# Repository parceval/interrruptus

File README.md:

# interrruptus
A simple Interrupt Controller and Timer made in Verilog

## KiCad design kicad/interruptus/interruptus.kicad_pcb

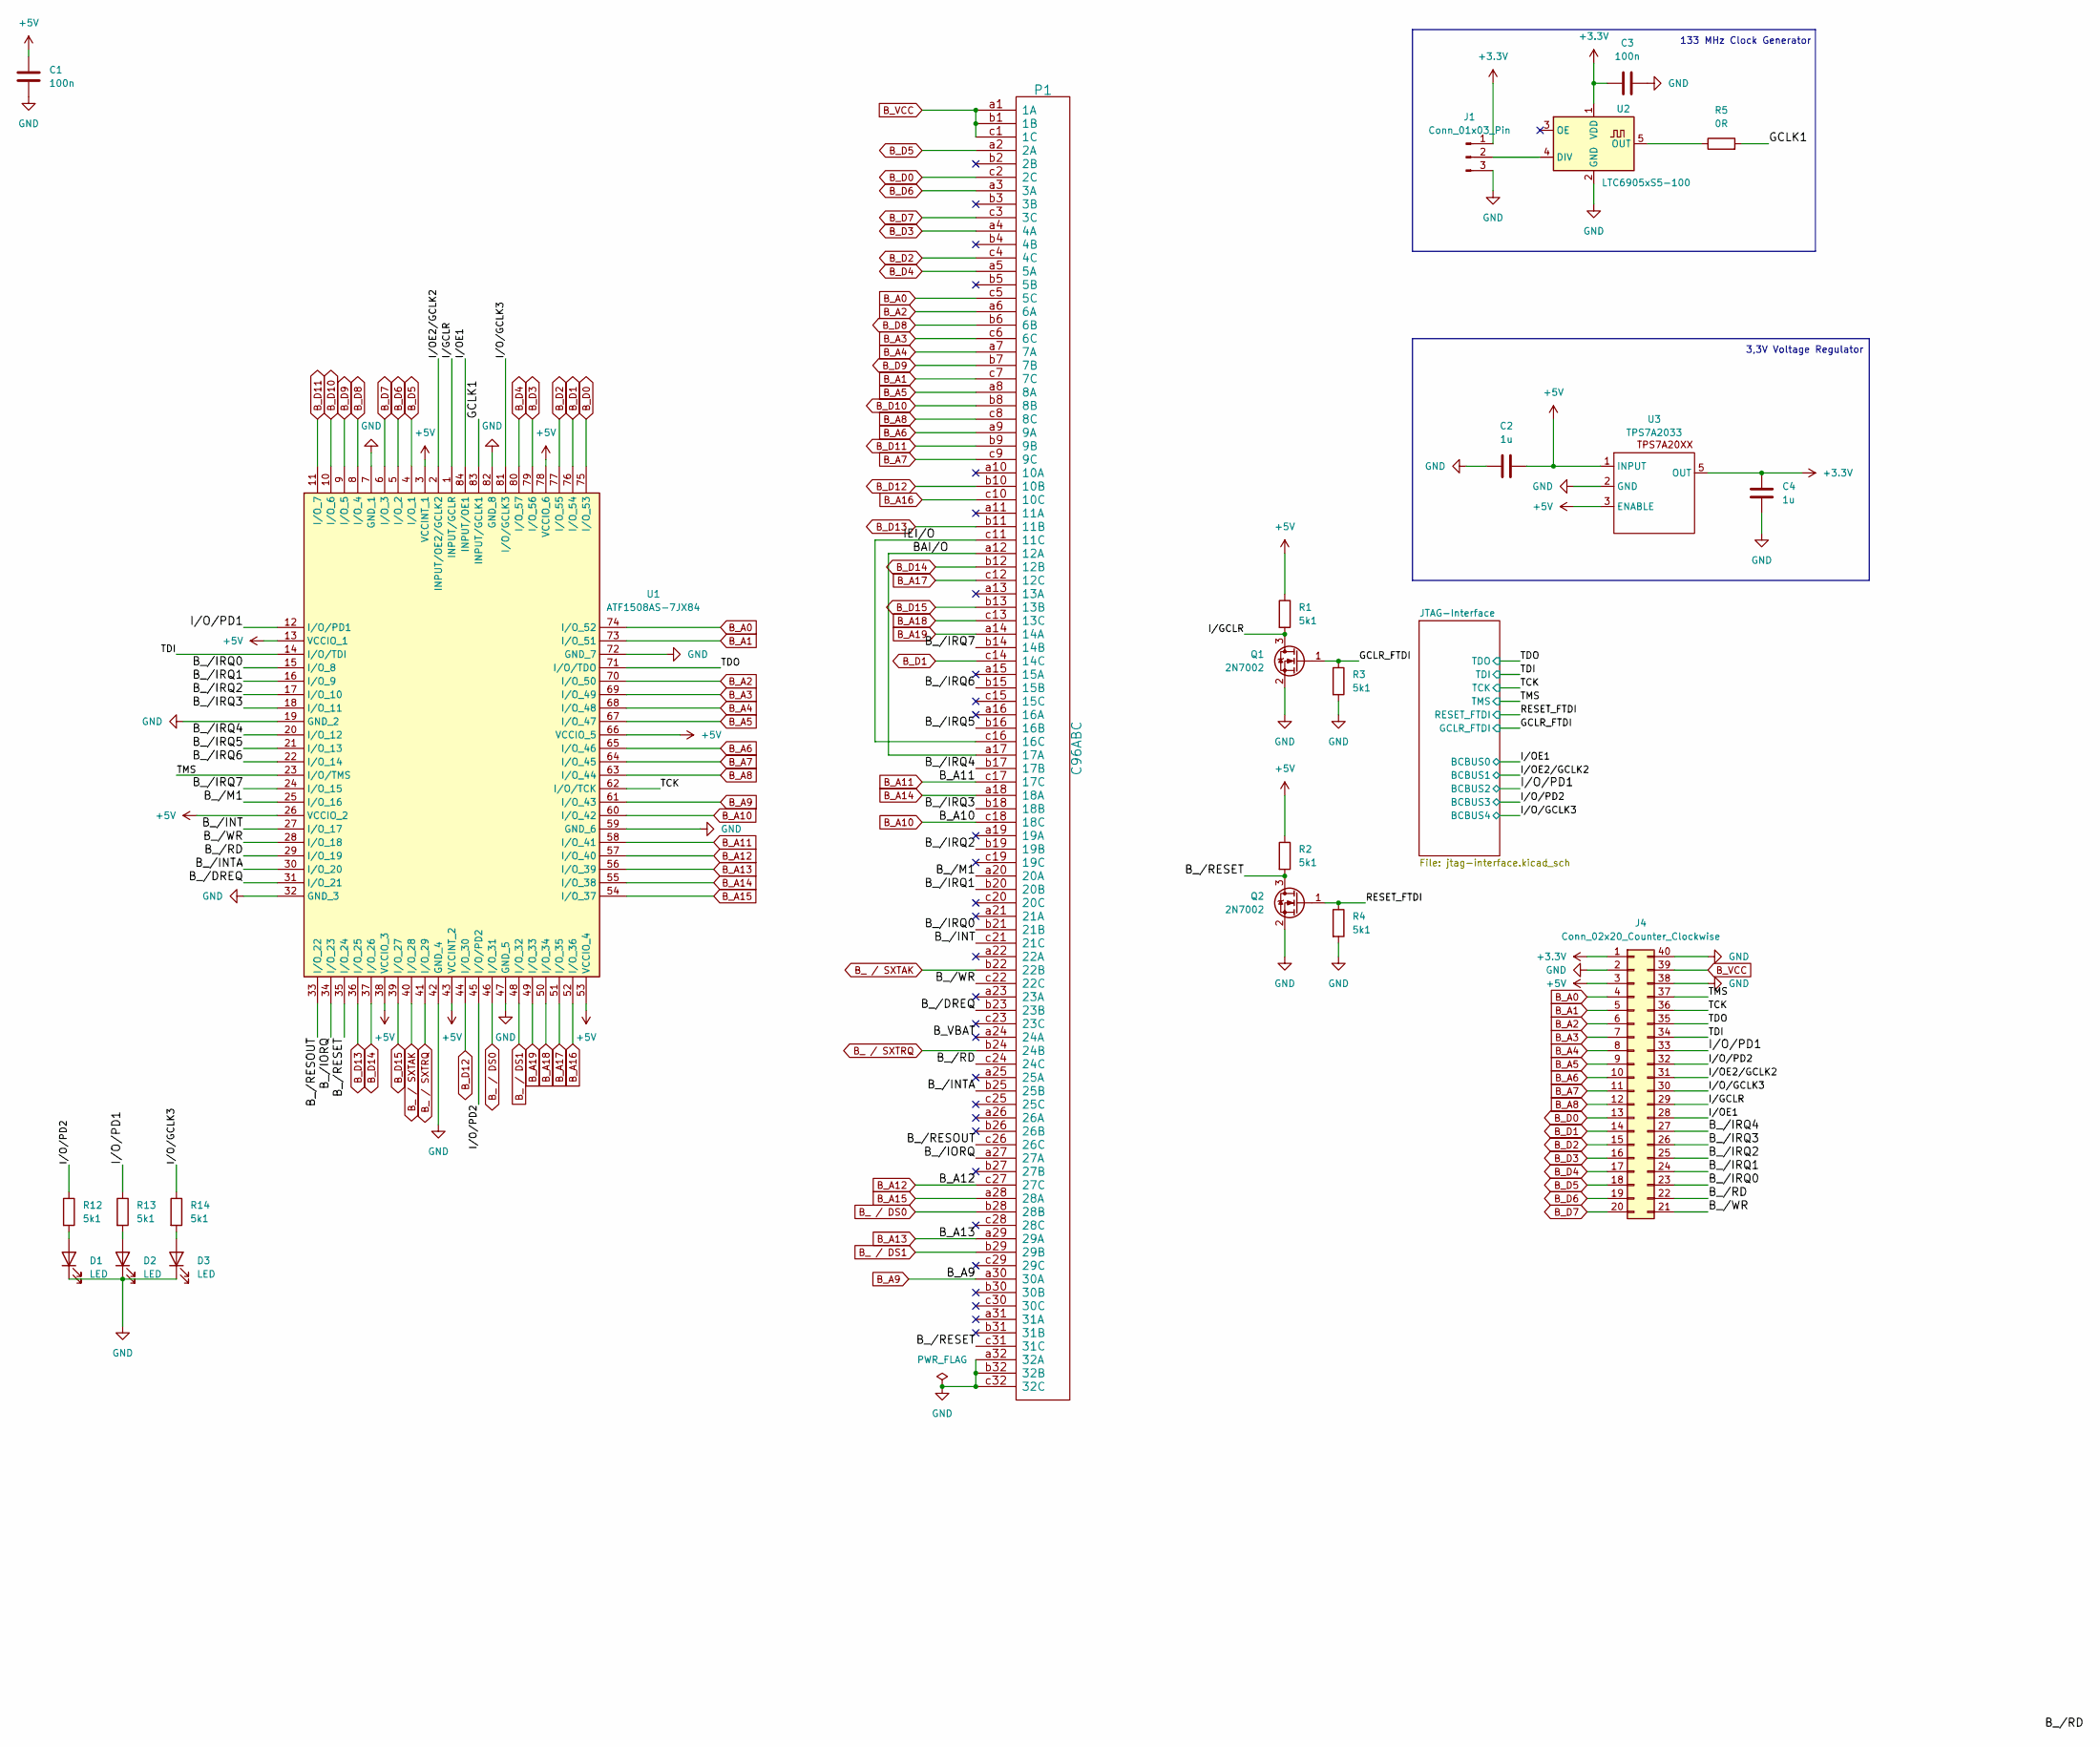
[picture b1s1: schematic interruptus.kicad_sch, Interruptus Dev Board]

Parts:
C1, C3: 100n; C_0603_1608Metric_Pad1.08x0.95mm_HandSolder
C2, C4: 1u; C_0603_1608Metric_Pad1.08x0.95mm_HandSolder
D1, D2, D3: LED; LED_0603_1608Metric_Pad1.05x0.95mm_HandSolder
J1: Conn_01x03_Pin; PinHeader_1x03_P2.54mm_Vertical
J4: Conn_02x20_Counter_Clockwise; PinHeader_2x20_P2.54mm_Vertical
P1: C96ABC; DIN41612_R_3x32_Female_Horizontal_THT
Q1, Q2: 2N7002; SOT-23
R1, R2, R3, R4, R12, R13, R14: 5k1; R_0603_1608Metric_Pad0.98x0.95mm_HandSolder
R5: 0R; R_0603_1608Metric_Pad0.98x0.95mm_HandSolder
U1: ATF1508AS-7JX84; PLCC-84_THT-Socket; Manufacturer_Part_Number ATF1508AS-7JX84; Mouser Part Number 556-ATF1508AS-7JX84
U2: LTC6905xS5-100; TSOT-23-5
U3: TPS7A2033; SOT-23-5

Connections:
+3.3V: C3.1, C4.1, J1.1, J4.1, U2.1 (VDD), U3.5 (OUT)
+5V: C1.1, C2.2, J4.3, R1.1, R2.1, U1.3 (VCCINT_1), U1.13 (VCCIO_1), U1.26 (VCCIO_2), U1.38 (VCCIO_3), U1.43 (VCCINT_2), U1.53 (VCCIO_4), U1.66 (VCCIO_5), U1.78 (VCCIO_6), U3.1 (INPUT), U3.3 (ENABLE); also elsewhere on the board
/BAI/O: P1.a12 (12A), P1.a17 (17A)
/B_VBAT: P1.a24 (24A)
/B_/DREQ: P1.b23 (23B), U1.31 (I/O_21)
/B_/INT: P1.c21 (21C), U1.27 (I/O_17)
/B_/INTA: P1.b25 (25B), U1.30 (I/O_20)
/B_/IORQ: P1.a27 (27A), U1.34 (I/O_23)
/B_/IRQ0: J4.23, P1.b21 (21B), U1.15 (I/O_8)
/B_/IRQ1: J4.24, P1.b20 (20B), U1.16 (I/O_9)
/B_/IRQ2: J4.25, P1.b19 (19B), U1.17 (I/O_10)
/B_/IRQ3: J4.26, P1.b18 (18B), U1.18 (I/O_11)
/B_/IRQ4: J4.27, P1.b17 (17B), U1.20 (I/O_12)
/B_/IRQ5: P1.b16 (16B), U1.21 (I/O_13)
/B_/IRQ6: P1.b15 (15B), U1.22 (I/O_14)
/B_/IRQ7: P1.b14 (14B), U1.24 (I/O_15)
/B_/M1: P1.a20 (20A), U1.25 (I/O_16)
/B_/RD: J4.22, P1.c24 (24C), U1.29 (I/O_19)
/B_/RESET: P1.c31 (31C), Q2.3 (D), R2.2, U1.35 (I/O_24)
/B_/RESOUT: P1.c26 (26C), U1.33 (I/O_22)
/B_/WR: J4.21, P1.c22 (22C), U1.28 (I/O_18)
/GCLK1: R5.2, U1.83 (INPUT/GCLK1)
/GCLR_FTDI: Q1.1 (G), R3.1; also elsewhere on the board
/IEI/O: P1.c11 (11C), P1.c16 (16C)
/I/GCLR: J4.29, Q1.3 (D), R1.2, U1.1 (INPUT/GCLR)
/I/OE1: J4.28, U1.84 (INPUT/OE1); also elsewhere on the board
/I/OE2/GCLK2: J4.31, U1.2 (INPUT/OE2/GCLK2); also elsewhere on the board
/I/O/GCLK3: J4.30, R14.1, U1.81 (I/O/GCLK3); also elsewhere on the board
/I/O/PD1: J4.33, R13.1, U1.12 (I/O/PD1); also elsewhere on the board
/I/O/PD2: J4.32, R12.1, U1.45 (I/O/PD2); also elsewhere on the board
/RESET_FTDI: Q2.1 (G), R4.1; also elsewhere on the board
/TCK: J4.36, U1.62 (I/O/TCK); also elsewhere on the board
/TDI: J4.34, U1.14 (I/O/TDI); also elsewhere on the board
/TDO: J4.35, U1.71 (I/O/TDO); also elsewhere on the board
/TMS: J4.37, U1.23 (I/O/TMS); also elsewhere on the board
B_ / DS0: P1.b28 (28B), U1.46 (I/O_31)
B_ / DS1: P1.b29 (29B), U1.48 (I/O_32)
B_ / SXTAK: P1.b22 (22B), U1.40 (I/O_28)
B_ / SXTRQ: P1.b24 (24B), U1.41 (I/O_29)
B_A0: J4.4, P1.c5 (5C), U1.74 (I/O_52)
B_A1: J4.5, P1.c7 (7C), U1.73 (I/O_51)
B_A2: J4.6, P1.a6 (6A), U1.70 (I/O_50)
B_A3: J4.7, P1.c6 (6C), U1.69 (I/O_49)
B_A4: J4.8, P1.a7 (7A), U1.68 (I/O_48)
B_A5: J4.9, P1.a8 (8A), U1.67 (I/O_47)
B_A6: J4.10, P1.a9 (9A), U1.65 (I/O_46)
B_A7: J4.11, P1.c9 (9C), U1.64 (I/O_45)
B_A8: J4.12, P1.c8 (8C), U1.63 (I/O_44)
B_A9: P1.a30 (30A), U1.61 (I/O_43)
B_A10: P1.c18 (18C), U1.60 (I/O_42)
B_A11: P1.c17 (17C), U1.58 (I/O_41)
B_A12: P1.c27 (27C), U1.57 (I/O_40)
B_A13: P1.a29 (29A), U1.56 (I/O_39)
B_A14: P1.a18 (18A), U1.55 (I/O_38)
B_A15: P1.a28 (28A), U1.54 (I/O_37)
B_A16: P1.c10 (10C), U1.52 (I/O_36)
B_A17: P1.c12 (12C), U1.51 (I/O_35)
B_A18: P1.c13 (13C), U1.50 (I/O_34)
B_A19: P1.a14 (14A), U1.49 (I/O_33)
B_D0: J4.13, P1.c2 (2C), U1.75 (I/O_53); also elsewhere on the board
B_D1: J4.14, P1.c14 (14C), U1.76 (I/O_54); also elsewhere on the board
B_D2: J4.15, P1.c4 (4C), U1.77 (I/O_55); also elsewhere on the board
B_D3: J4.16, P1.a4 (4A), U1.79 (I/O_56); also elsewhere on the board
B_D4: J4.17, P1.a5 (5A), U1.80 (I/O_57); also elsewhere on the board
B_D5: J4.18, P1.a2 (2A), U1.4 (I/O_1); also elsewhere on the board
B_D6: J4.19, P1.a3 (3A), U1.5 (I/O_2); also elsewhere on the board
B_D7: J4.20, P1.c3 (3C), U1.6 (I/O_3); also elsewhere on the board
B_D8: P1.b6 (6B), U1.8 (I/O_4)
B_D9: P1.b7 (7B), U1.9 (I/O_5)
B_D10: P1.b8 (8B), U1.10 (I/O_6)
B_D11: P1.b9 (9B), U1.11 (I/O_7)
B_D12: P1.b10 (10B), U1.44 (I/O_30)
B_D13: P1.b11 (11B), U1.36 (I/O_25)
B_D14: P1.b12 (12B), U1.37 (I/O_26)
B_D15: P1.b13 (13B), U1.39 (I/O_27)
B_VCC: J4.39, P1.a1 (1A), P1.b1 (1B), P1.c1 (1C); also elsewhere on the board
GND: C1.2, C2.1, C3.2, C4.2, D1.1 (K), D2.1 (K), D3.1 (K), J1.3, J4.2, J4.38, J4.40, P1.a32 (32A), P1.b32 (32B), P1.c32 (32C), Q1.2 (S), Q2.2 (S), R3.2, R4.2, U1.7 (GND_1), U1.19 (GND_2), U1.32 (GND_3), U1.42 (GND_4), U1.47 (GND_5), U1.59 (GND_6), U1.72 (GND_7), U1.82 (GND_8), U2.2 (GND), U3.2 (GND); also elsewhere on the board
unnamed: D1.2 (A), R12.2
unnamed: D2.2 (A), R13.2
unnamed: D3.2 (A), R14.2
unnamed: J1.2, U2.4 (DIV)
unnamed: R5.1, U2.5 (OUT)

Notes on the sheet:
133 MHz Clock Generator
3,3V Voltage Regulator

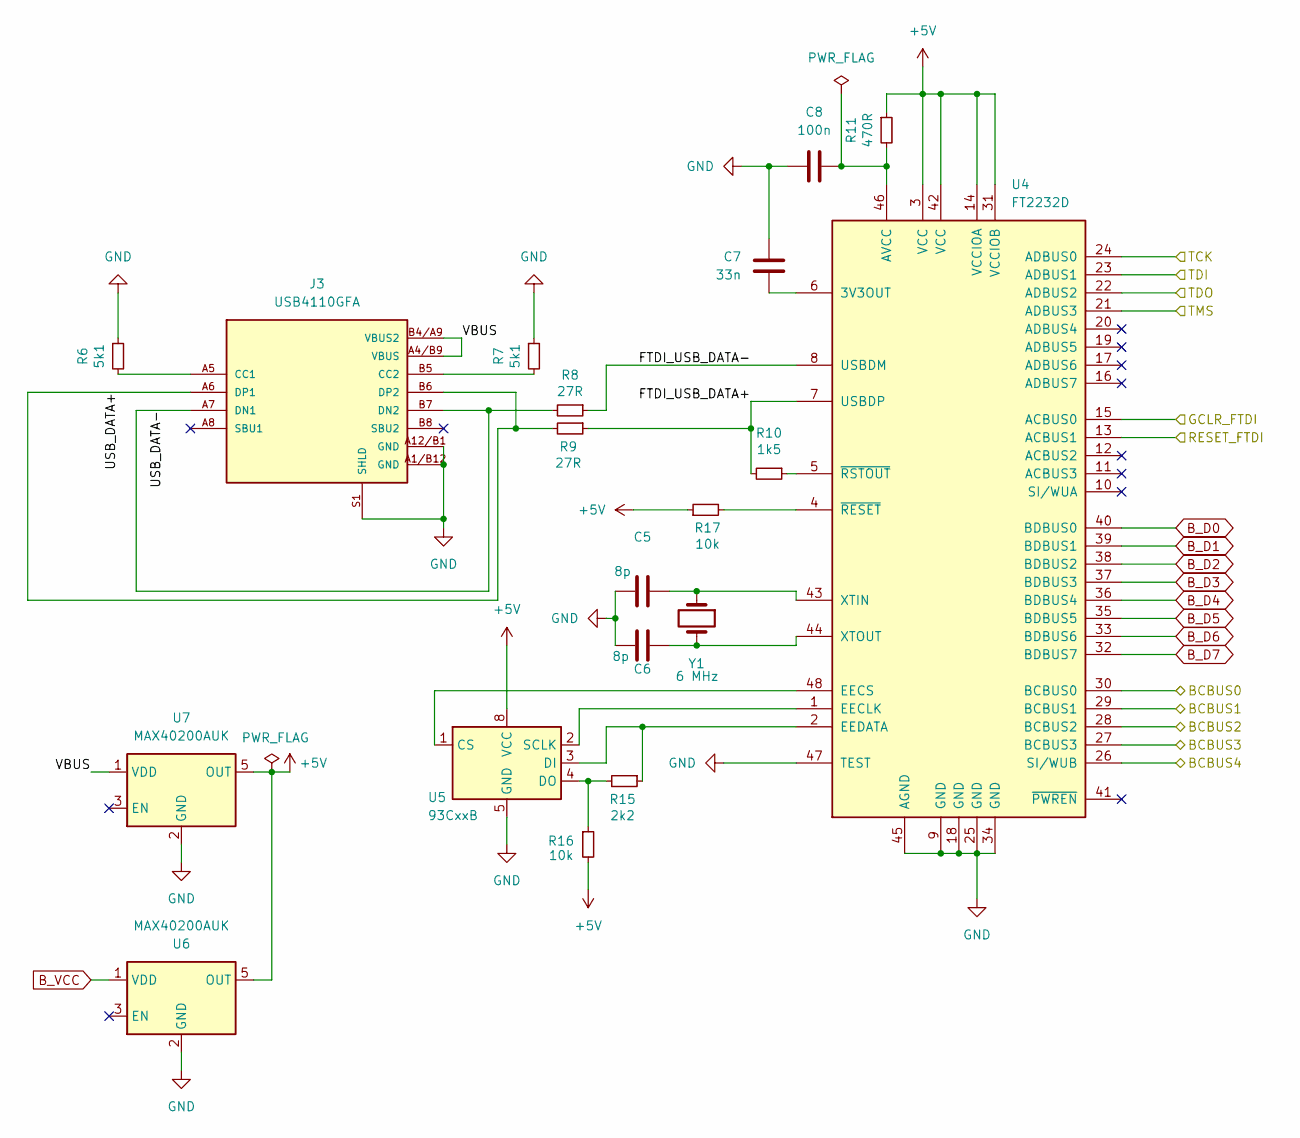
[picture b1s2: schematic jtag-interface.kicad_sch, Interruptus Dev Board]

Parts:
C5, C6: 8p; C_0603_1608Metric_Pad1.08x0.95mm_HandSolder
C7: 33n; C_0603_1608Metric_Pad1.08x0.95mm_HandSolder
C8: 100n; C_0603_1608Metric_Pad1.08x0.95mm_HandSolder
J3: USB4110GFA; USB_C_Receptacle_GCT_USB4110
R6, R7: 5k1; R_0603_1608Metric_Pad0.98x0.95mm_HandSolder
R8, R9: 27R; R_0603_1608Metric_Pad0.98x0.95mm_HandSolder
R10: 1k5; R_0603_1608Metric_Pad0.98x0.95mm_HandSolder
R11: 470R; R_0603_1608Metric_Pad0.98x0.95mm_HandSolder
R15: 2k2; R_0603_1608Metric_Pad0.98x0.95mm_HandSolder
R16, R17: 10k; R_0603_1608Metric_Pad0.98x0.95mm_HandSolder
U4: FT2232D; LQFP-48_7x7mm_P0.5mm
U5: 93CxxB; SOIC-8_3.9x4.9mm_P1.27mm
U6, U7: MAX40200AUK; SOT-23-5
Y1: 6 MHz; Crystal_SMD_8045-2Pin_8.0x4.5mm_HandSoldering

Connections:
+5V: R11.1, R16.2, R17.1, U4.3 (VCC), U4.14 (VCCIOA), U4.31 (VCCIOB), U4.42 (VCC), U5.8 (VCC), U6.5 (OUT), U7.5 (OUT); also elsewhere on the board
/GCLR_FTDI: U4.15 (ACBUS0); also elsewhere on the board
/I/OE1: U4.30 (BCBUS0); also elsewhere on the board
/I/OE2/GCLK2: U4.29 (BCBUS1); also elsewhere on the board
/I/O/GCLK3: U4.26 (SI/WUB); also elsewhere on the board
/I/O/PD1: U4.28 (BCBUS2); also elsewhere on the board
/I/O/PD2: U4.27 (BCBUS3); also elsewhere on the board
/JTAG-Interface/FTDI_USB_DATA+: R9.1, R10.2, U4.7 (USBDP)
/JTAG-Interface/FTDI_USB_DATA-: R8.1, U4.8 (USBDM)
/JTAG-Interface/USB_DATA+: J3.A6 (DP1), J3.B6 (DP2), R9.2
/JTAG-Interface/USB_DATA-: J3.A7 (DN1), J3.B7 (DN2), R8.2
/JTAG-Interface/VBUS: J3.A4/B9 (VBUS), J3.B4/A9 (VBUS2), U7.1 (VDD)
/RESET_FTDI: U4.13 (ACBUS1); also elsewhere on the board
/TCK: U4.24 (ADBUS0); also elsewhere on the board
/TDI: U4.23 (ADBUS1); also elsewhere on the board
/TDO: U4.22 (ADBUS2); also elsewhere on the board
/TMS: U4.21 (ADBUS3); also elsewhere on the board
B_D0: U4.40 (BDBUS0); also elsewhere on the board
B_D1: U4.39 (BDBUS1); also elsewhere on the board
B_D2: U4.38 (BDBUS2); also elsewhere on the board
B_D3: U4.37 (BDBUS3); also elsewhere on the board
B_D4: U4.36 (BDBUS4); also elsewhere on the board
B_D5: U4.35 (BDBUS5); also elsewhere on the board
B_D6: U4.33 (BDBUS6); also elsewhere on the board
B_D7: U4.32 (BDBUS7); also elsewhere on the board
B_VCC: U6.1 (VDD); also elsewhere on the board
GND: C5.1, C6.1, C7.1, C8.1, J3.A1/B12 (GND), J3.A12/B1 (GND), J3.S1 (SHLD), R6.1, R7.1, U4.9 (GND), U4.18 (GND), U4.25 (GND), U4.34 (GND), U4.45 (AGND), U4.47 (TEST), U5.5 (GND), U6.2 (GND), U7.2 (GND); also elsewhere on the board
unnamed: J3.A5 (CC1), R6.2
unnamed: J3.B5 (CC2), R7.2
unnamed: C7.2, U4.6 (3V3OUT)
unnamed: C8.2, R11.2, U4.46 (AVCC)
unnamed: U4.1 (EECLK), U5.2 (SCLK)
unnamed: U4.48 (EECS), U5.1 (CS)
unnamed: R15.1, U4.2 (EEDATA), U5.3 (DI)
unnamed: C5.2, U4.43 (XTIN), Y1.1
unnamed: C6.2, U4.44 (XTOUT), Y1.2
unnamed: R17.2, U4.4 (~RESET)
unnamed: R10.1, U4.5 (~RSTOUT)
unnamed: R15.2, R16.1, U5.4 (DO)

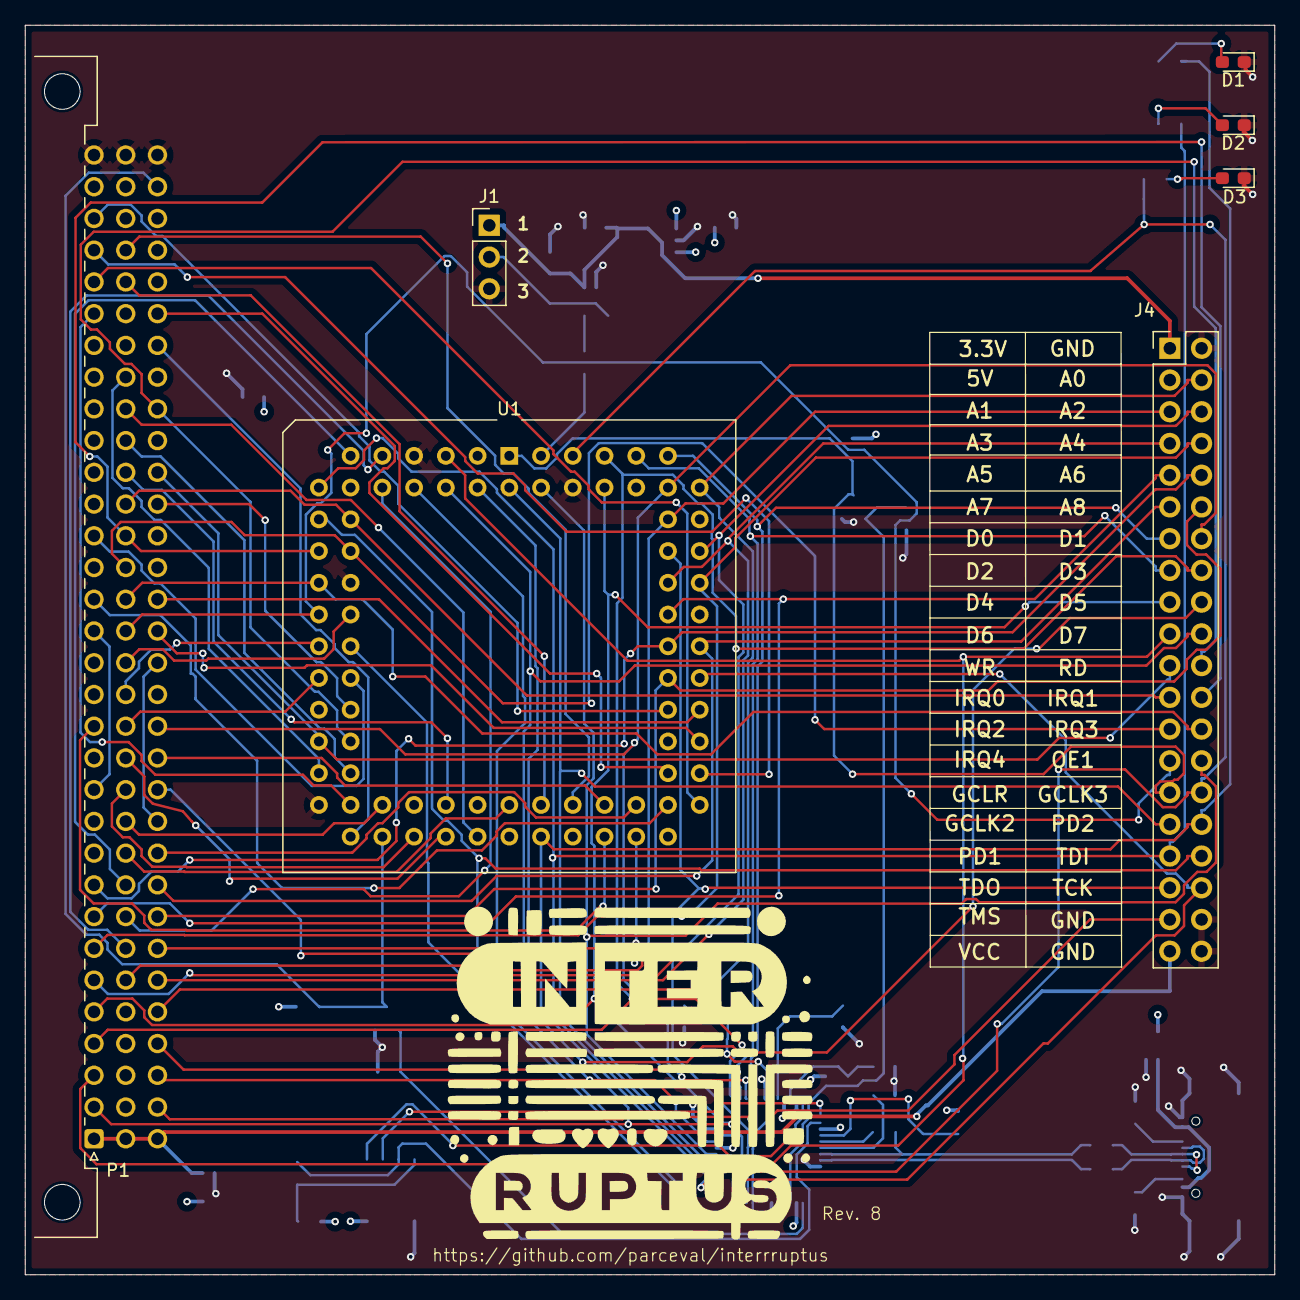
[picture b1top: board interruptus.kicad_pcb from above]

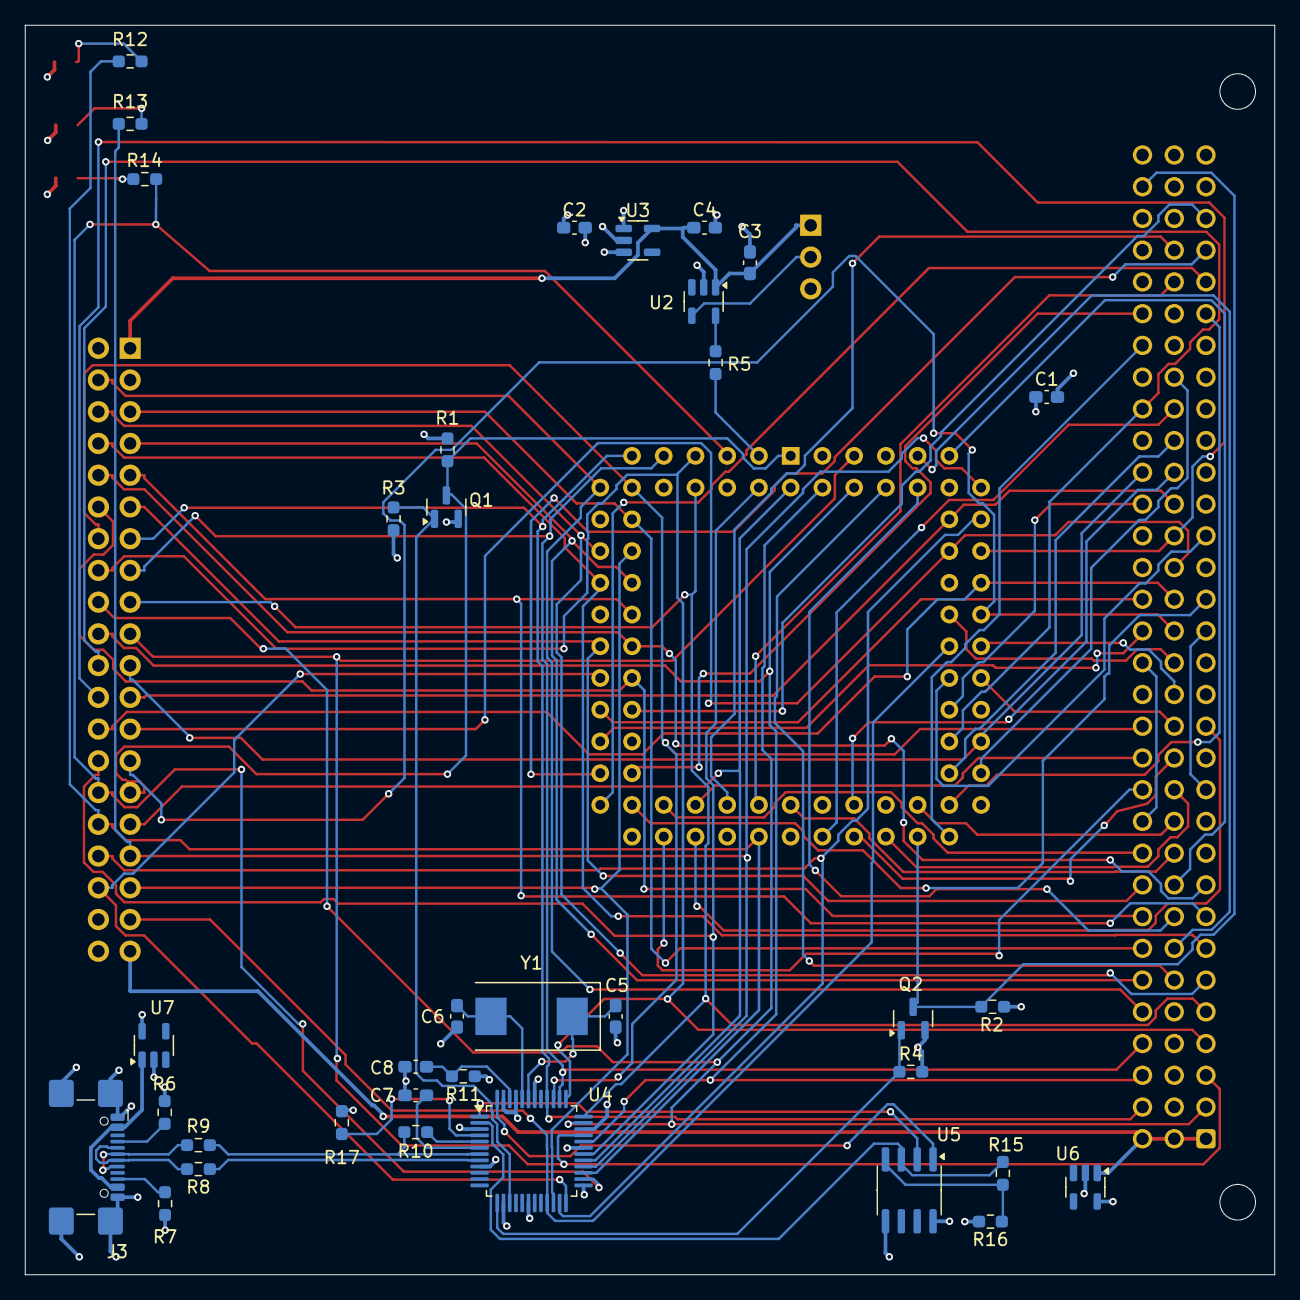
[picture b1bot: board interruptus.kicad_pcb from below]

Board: 4 copper layers, 100.0 x 100.0 mm, 42 parts (35 on the bottom side), 98 nets.

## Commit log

2024-05-26 initial import
2024-05-26 kicad stuff
2024-05-30 small changes
2024-05-31 new usb connector, and other changes
2024-06-12 rev 5
2024-06-15 rev 8
2024-08-30 Add .gitignore
2024-08-30 .gitignore more
2024-08-30 Add Makefile
2024-08-30 Add openocd.cfg atdh1150usb.cfg
2024-08-30 This address decoding does not yet work
2024-09-02 added a testbench. code fixes to make it work in testbench
